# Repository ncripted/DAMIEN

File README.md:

# DAMIEN | Omni UGV

DAMIEN is a miniature omnidirectional camera rover with three independently driven omni wheels. The PCB doubles as the chassis. The design uses an ESP32-S3, a ribbon-connected camera, and a single-cell LiPo power system with USB charging and programming.

## Open the design

Open [the Rev F KiCad project](outputs/rover/Omni_UGV_Rev_F_power_rebuild/omni_ugv.kicad_pro) in KiCad. The project contains the editable schematics, board, and project-local footprint library. See the [routing checkpoint](outputs/rover/Omni_UGV_Rev_F_power_rebuild/START_HERE.md) and the [latest KiCad DRC report](outputs/rover/Omni_UGV_Rev_F_power_rebuild/drc.json).

## Prototype status

**Fabrication is on hold.** The saved Rev F rebuild has 19 open connections and 7 dangling traces. The remaining work includes charger, battery-protector, and eFuse routing, plus electrical review of the motor-current path, braking transients, and short-circuit recovery.

## Repository contents

- [Board revisions and review packages](outputs/rover/) include earlier designs and intermediate candidates.
- [Development and validation work](work/) includes layout experiments, routing scripts, and engineering checks.

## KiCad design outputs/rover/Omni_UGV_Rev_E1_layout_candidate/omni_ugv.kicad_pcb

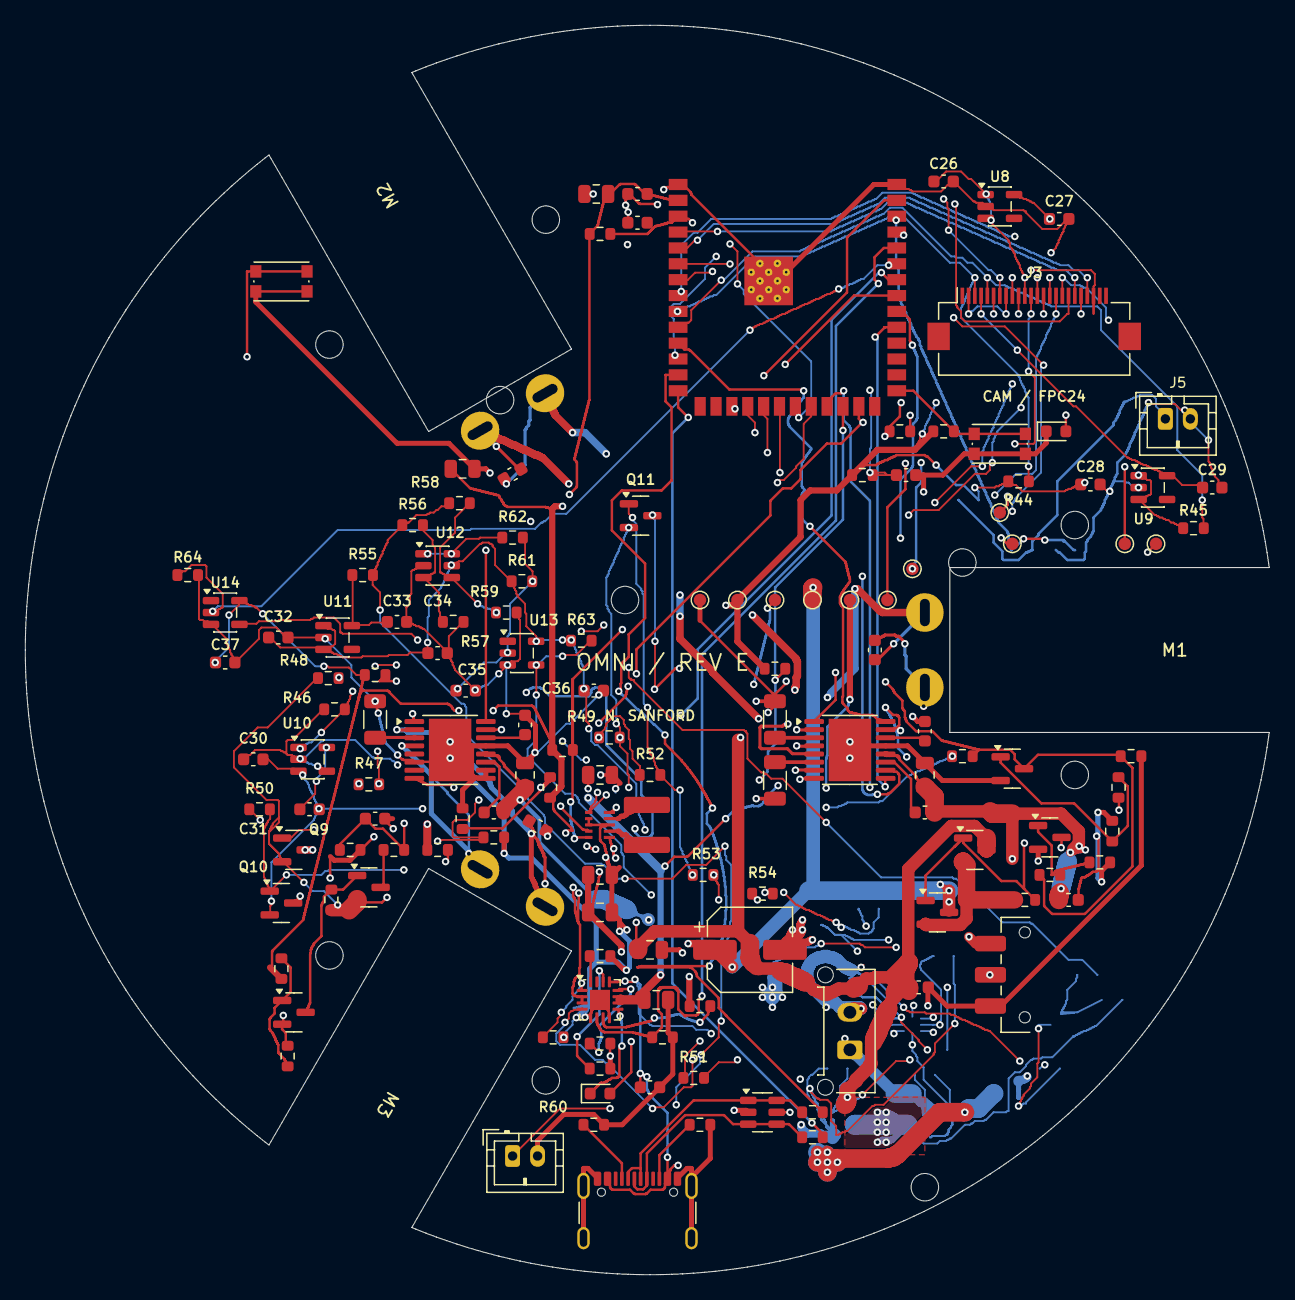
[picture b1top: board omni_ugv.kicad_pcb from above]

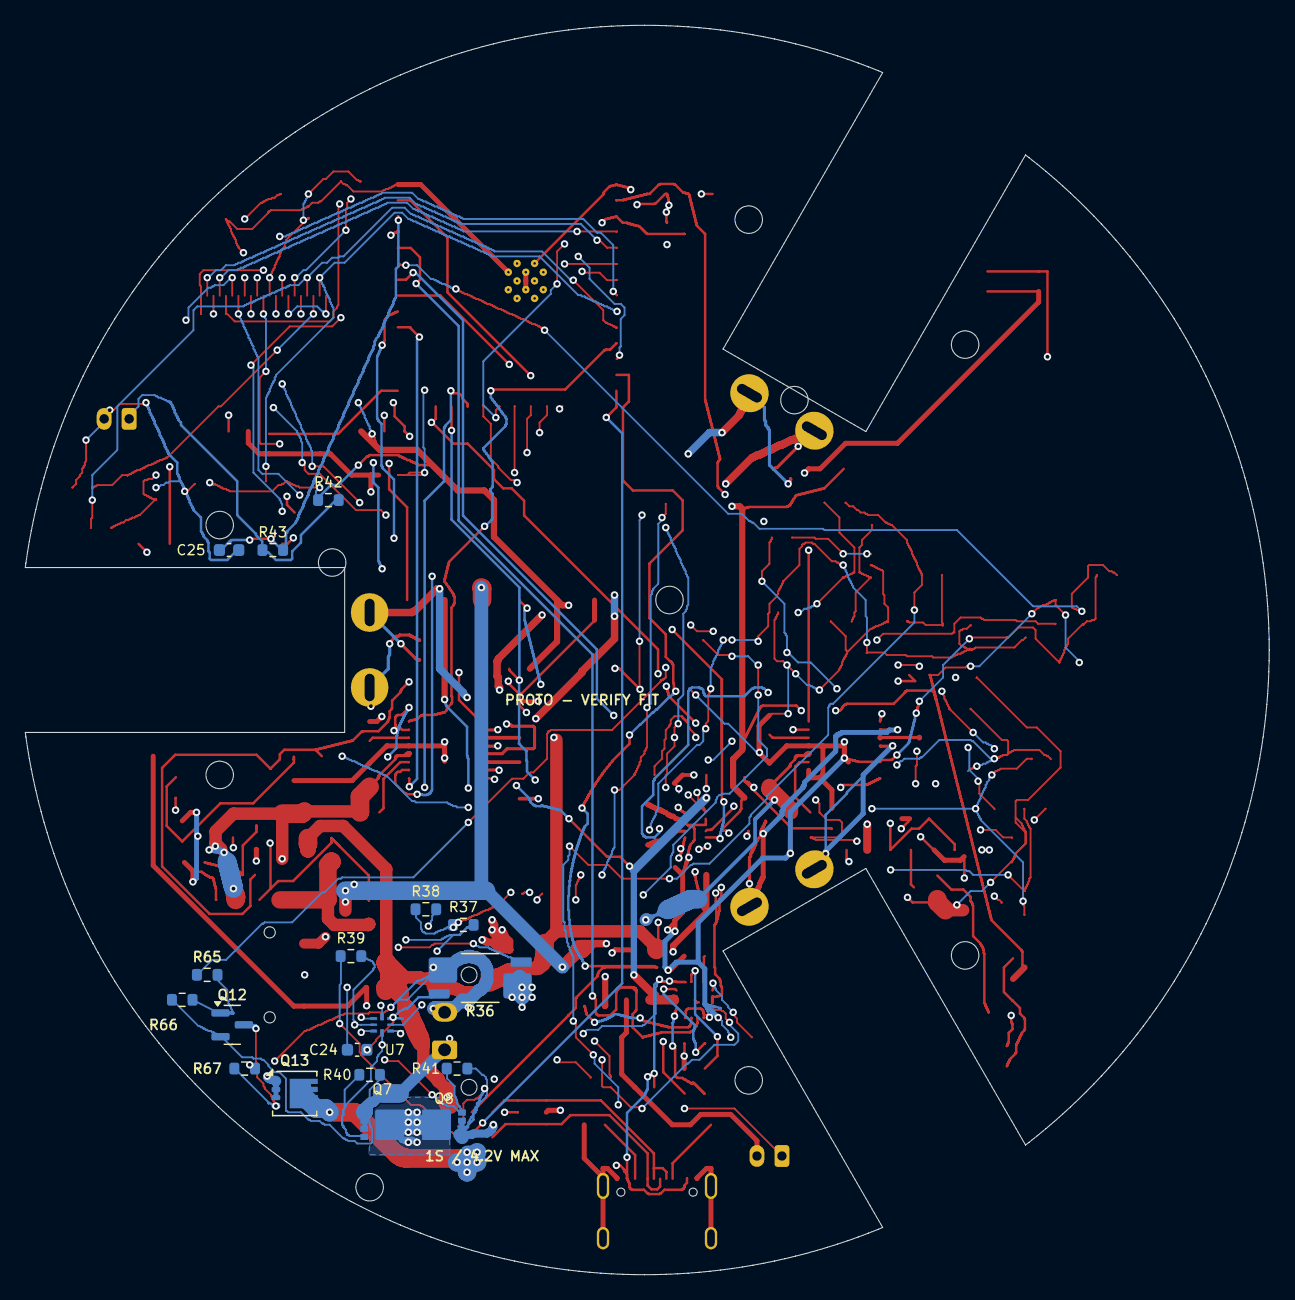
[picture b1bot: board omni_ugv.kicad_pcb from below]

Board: 4 copper layers, 99.6 x 100.0 mm, 167 parts (18 on the bottom side), 107 nets.

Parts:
C1, C15, C21: 1u/10V; Capacitor_SMD__C_0603_1608Metric
C2, C5, C6, C9, C16, C17: 10u/10V; Capacitor_SMD__C_0805_2012Metric
C3, C4, C22, C23: 100n/16V; Capacitor_SMD__C_0603_1608Metric
C7, C10: 2.2u/10V; Capacitor_SMD__C_0603_1608Metric
C8, C11: 10n/25V; Capacitor_SMD__C_0603_1608Metric
C12, C13, C14: 100n/25V; Capacitor_SMD__C_0603_1608Metric
C18, C19, C20: 22u/10V X5R 20%; Capacitor_SMD__C_0805_2012Metric
C24, C25: 100n/16V X7R; Capacitor_SMD__C_0603_1608Metric
C26, C27, C28, C29, C32, C33: 2.2u/10V X7R; Capacitor_SMD__C_0603_1608Metric
C30, C31, C34, C36, C37: 100n/10V X7R; Capacitor_SMD__C_0603_1608Metric
C35: 220n/10V X7R; Capacitor_SMD__C_0603_1608Metric
C90: 220u/10V; CP_Elec_6.3x5.8_HandAssembly
D1: STATUS GREEN; LED_SMD__LED_0603_1608Metric
D2: CHARGE AMBER; LED_SMD__LED_0603_1608Metric
H1, H2, H3, H4, H5, H6, H7, H8, H9, H10: M2; MountingHole_2.2mm_M2
J1: USB-C; Connector_USB__USB_C_Receptacle_GCT_USB4105-xx-A_16P_TopMnt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
J2: RAW 1S CELL 4.2V MAX; Connector_Molex__Molex_Micro-Fit_3.0_43650-0215_1x02_P3.00m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
J3: M0031 CAMERA FPC24; Camera_FH12_24
J4: CELL NTC - CHARGER; Connector_JST__JST_PH_B2B-PH-K_1x02_P2.00mm_Vertical
J5: CELL NTC - DRIVE; Connector_JST__JST_PH_B2B-PH-K_1x02_P2.00mm_Vertical
L1: 0.47uH/5.4A; L_XFL4015
M1: POLOLU 3065 MOTOR 1; Pololu_HPCB_Solder
M2: POLOLU 3065 MOTOR 2; Pololu_HPCB_Solder
M3: POLOLU 3065 MOTOR 3; Pololu_HPCB_Solder
Q1, Q2: DMP2035U-7; Package_TO_SOT_SMD__SOT-23
Q3, Q4, Q6, Q10, Q11: MMBT3904; Package_TO_SOT_SMD__SOT-23
Q5: AO3401A; Package_TO_SOT_SMD__SOT-23
Q7, Q8: CSD17308Q3; CSD17308Q3_TI
Q9, Q12: MMBT3906; Package_TO_SOT_SMD__SOT-23
Q13: DMP2008UFG-7; Discharge_PowerDI3333_8
R1, R2, R4, R5, R8, R29, R54: 10k; Resistor_SMD__R_0603_1608Metric
R3, R27, R62: 1k; Resistor_SMD__R_0603_1608Metric
R6, R7, R9: 0.25R/0.5W; Resistor_SMD__R_1206_3216Metric
R10, R11: 5.1k; Resistor_SMD__R_0603_1608Metric
R12, R13: 22R; Resistor_SMD__R_0603_1608Metric
R14: 3.57k; Resistor_SMD__R_0603_1608Metric
R15: 3.24k; Resistor_SMD__R_0603_1608Metric
R16: 46.4k; Resistor_SMD__R_0603_1608Metric
R17, R19, R22, R23, R26, R30, R31, R33, R34, R35, R46, R48, R61, R63, R64: 100k; Resistor_SMD__R_0603_1608Metric
R18: 2.2k; Resistor_SMD__R_0603_1608Metric
R20: 511k; Resistor_SMD__R_0603_1608Metric
R21: 91k; Resistor_SMD__R_0603_1608Metric
R24, R47: 22k; Resistor_SMD__R_0603_1608Metric
R25, R67: 56k; Resistor_SMD__R_0603_1608Metric
R28, R49, R51, R53, R66: 1M; Resistor_SMD__R_0603_1608Metric
R32, R65: 47k; Resistor_SMD__R_0603_1608Metric
R36: 10m 1% 1W KELVIN; WSK2512_T1p19_Kelvin
R37: 100R 1%; Resistor_SMD__R_0603_1608Metric
R38: 20R 1%; Resistor_SMD__R_0603_1608Metric
R39, R43: 1k 1%; Resistor_SMD__R_0603_1608Metric
R40, R41: 10M; Resistor_SMD__R_0603_1608Metric
R42, R55, R60: 10k 1%; Resistor_SMD__R_0603_1608Metric
R44, R45: 4.7k; Resistor_SMD__R_0603_1608Metric
R50: 33k; Resistor_SMD__R_0603_1608Metric
R52: 3.3k; Resistor_SMD__R_0603_1608Metric
R56: 200k 1%; Resistor_SMD__R_0603_1608Metric
R57, R59: 100k 1%; Resistor_SMD__R_0603_1608Metric
R58: 442k 1%; Resistor_SMD__R_0603_1608Metric
SW1: RESET; Button_Switch_SMD__SW_Push_1P1T_NO_CK_KMR2
SW2: BOOT; Button_Switch_SMD__SW_Push_1P1T_NO_CK_KMR2
SW3: POWER; Button_Switch_SMD__SW_SPDT_CK_JS102011SAQN
TP1: GND; TestPoint__TestPoint_Pad_D1.0mm
TP2: +3V3; TestPoint__TestPoint_Pad_D1.0mm
TP3: VBAT; TestPoint__TestPoint_Pad_D1.0mm
TP4: VMOTOR; TestPoint__TestPoint_Pad_D1.0mm
TP5: SYS_RAW; TestPoint__TestPoint_Pad_D1.0mm
TP6: ESP_EN; TestPoint__TestPoint_Pad_D1.0mm
TP7: LED_STATUS; TestPoint__TestPoint_Pad_D1.0mm
TP8: DRIVE_ENABLE; TestPoint__TestPoint_Pad_D1.0mm
TP9: FAULT_U2; TestPoint__TestPoint_Pad_D1.0mm
TP10: FAULT_U3; TestPoint__TestPoint_Pad_D1.0mm
TP11: REG_PG; TestPoint__TestPoint_Pad_D1.0mm
U1: ESP32-S3-WROOM-1-N8R8; RF_Module__ESP32-S3-WROOM-1
U2, U3: DRV8833PWP; Package_SO__HTSSOP-16-1EP_4.4x5mm_P0.65mm_EP3.4x5mm_Mask2.4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
U4: TPS63802DLA; TPS63802_DLA0010A
U5: BQ24074RGT; Package_DFN_QFN__VQFN-16-1EP_3x3mm_P0.5mm_EP1.6x1.6mm
U6: USBLC6-2SC6; Package_TO_SOT_SMD__SOT-23-6
U7: BQ298217RUGR; BQ298217_RUG0008A
U8: TLV75513PDBVR; Camera_SOT23_5
U9: TLV75528PDBVR; Camera_SOT23_5
U10: TPS3840DL31DBVR; Camera_SOT23_5
U11: TLV75533PDBVR; Camera_SOT23_5
U12: TLV6700DDCR; Power_SOT23_6
U13: SN74LVC1G14DBVR; Camera_SOT23_5
U14: SN74LVC1G17DBVR; Camera_SOT23_5

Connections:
+3V3: C2.1, C3.1, C5.1, C19.1, C20.1, C26.1, C28.1, C37.1, J3.11, R1.1, R2.1, R4.1, R5.1, R8.1, R19.1, R20.1, R22.1, R32.1, R42.1, R44.1, R45.1, TP2.1, U1.2, U4.6, U8.1, U8.3, U9.1, U9.3, U14.5
CAM_1V3: C27.1, J3.10, U8.5
CAM_2V8: C29.1, J3.4, U9.5
CAM_D0: J3.19, U1.4
CAM_D1: J3.21, U1.5
CAM_D2: J3.22, U1.6
CAM_D3: J3.20, U1.7
CAM_D4: J3.18, U1.12
CAM_D5: J3.16, U1.17
CAM_D6: J3.14, U1.18
CAM_D7: J3.12, U1.19
CAM_HREF: J3.9, U1.22
CAM_PCLK: J3.17, U1.20
CAM_RESET: C4.1, J3.6, R4.2
CAM_SCL: J3.5, R45.2, U1.10
CAM_SDA: J3.3, R44.2, U1.9
CAM_VSYNC: J3.7, U1.21
CAM_XCLK: J3.13, U1.8
CELL_CHG_TEMP: J4.1, R55.2, R56.1, R58.1
CELL_N: C30.2, C31.2, J2.2, Q10.2, Q11.2, R36.1, R49.2, R51.2, R53.2, R67.2, U7.5, U10.3
CELL_P: C30.1, J2.1, Q7.1, Q7.2, Q7.3, Q12.2, R37.1, R38.1, R40.2, R46.1, R66.1, U10.2, U10.4
CELL_TEMP_ADC: C25.1, R43.2, U1.38
CELL_TEMP_DIV: J5.1, R42.2, R43.1
CELL_UV_CT: C31.1, U10.5
CELL_UV_EN_B: Q10.1, R50.2, R51.1
CELL_UV_FAULT: Q9.3, R49.1, R50.1, R52.1
CELL_UV_MOTOR_B: Q11.1, R52.2, R53.1
CELL_UV_PNP_B: Q9.1, R47.2, R48.2
CELL_UV_RESET_N: R46.2, R47.1, R65.1, U10.1
CHG_3V3: C33.1, R55.1, U11.5
CHG_COLD_SENSE: R58.2, R59.1, U12.4
CHG_DISABLE: R63.2, U5.4, U13.4
CHG_HOT_SENSE: R56.2, R57.1, U12.3
CHG_ILIM: R15.1, U5.12
CHG_ISET: R14.1, U5.16
CHG_LED_A: D2.2, R18.2
CHG_PGOOD: R19.2, U5.7
CHG_STATUS: D2.1, U5.9
CHG_TEMP_ALLOW_RC: C35.1, R61.2, R62.2, U13.2
CHG_TEMP_OK_OD: R62.1, U12.1, U12.6
CHG_TIMER: R16.1, U5.14
CHG_TS_BIAS: R60.1, U5.1
CUT_GATE: Q12.3, Q13.4, R67.1
CUT_PNP_B: Q12.1, R65.2, R66.2
DRIVE_ENABLE: Q4.3, Q11.3, R25.1, R27.2, R28.1, TP8.1, U2.1, U3.1
DRIVE_REQ: R27.1, U14.4
DRIVE_REQ_RAW: R64.1, U1.35, U14.2
ESP_BOOT: R2.2, SW2.1, U1.27
ESP_EN: C1.1, R1.2, SW1.1, TP6.1, U1.3
FAULT_U2: R5.2, TP9.1, U1.24, U2.8
FAULT_U3: R8.2, TP10.1, U1.25, U3.8
GND: C1.2, C2.2, C3.2, C4.2, C5.2, C6.2, C7.2, C9.2, C10.2, C15.2, C16.2, C17.2, C18.2, C19.2, C20.2, C21.2, C22.2, C23.2, C25.2, C26.2, C27.2, C28.2, C29.2, C32.2, C33.2, C34.2, C35.2, C36.2, C37.2, C90.2, D1.1, J1.A1, J1.A12, J1.B1, J1.B12, J1.S1, J3.2, J3.8, J3.15, J4.2, J5.2, Q3.2, Q4.2, Q6.2, R6.2, R7.2, R9.2, R10.2, R11.2, R14.2, R15.2, R16.2, R17.2, R21.2, R23.2, R26.2, R28.2, R30.2, R33.2, R35.2, R36.2, R57.2, R59.2, R60.2, R64.2, SW1.2, SW2.2, SW3.1, TP1.1, U1.1, U1.40, U1.41, U2.13, U2.17, U3.6, U3.9, U3.10, U3.13, U3.17, U4.2, U4.3, U4.8, U5.5, U5.8, U5.17, U6.2, U8.2, U9.2, U11.2, U12.2, U13.3, U14.3
LED_A: D1.2, R3.2
LED_STATUS: R3.1, TP7.1, U1.37
M1_A: C12.1, M1.1, U2.2
M1_B: C12.2, M1.2, U2.4
M1_IN1: U1.11, U2.16
M1_IN2: U1.23, U2.15
M1_SENSE: R6.1, U2.3
M2_A: C13.1, M2.1, U2.7
M2_B: C13.2, M2.2, U2.5
M2_IN1: U1.31, U2.9
M2_IN2: U1.32, U2.10
M2_SENSE: R7.1, U2.6
M3_A: C14.1, M3.1, U3.2
M3_B: C14.2, M3.2, U3.4
M3_IN1: U1.33, U3.16
M3_IN2: U1.34, U3.15
M3_SENSE: R9.1, U3.3
MEAS_BASE: Q6.1, R32.2, R33.1
MEAS_GATE: Q5.1, Q6.3, R31.2
MOTOR_BASE: Q3.1, R25.2, R26.1
MOTOR_GATE: Q1.1, Q2.1, Q3.3, R24.2
MOTOR_MID: Q1.2, Q2.2, R24.1
PROTECTED_RAW: Q8.1, Q8.2, Q8.3, Q13.1, Q13.2, Q13.3, R39.1, R41.2
PROT_BAT: R38.2, U7.1
PROT_CHG: Q7.4, R40.1, U7.8
PROT_CS_SENSE: R36.4, U7.4
PROT_DRAIN: Q7.5, Q7.6, Q7.7, Q7.8, Q7.9, Q8.5, Q8.6, Q8.7, Q8.8, Q8.9
PROT_DSG: Q8.4, R41.1, U7.7
PROT_PACK: R39.2, U7.6
PROT_VDD: C24.1, R37.2, U7.2
PROT_VSS_SENSE: C24.2, R36.3, U7.3
REG_FB: R20.2, R21.1, U4.4
REG_L1: L1.1, U4.9
REG_L2: L1.2, U4.7
REG_PG: R22.2, TP11.1, U4.5
SYS_ON: Q10.3, R23.1, R54.2, U4.1
SYS_ON_REQ: R54.1, SW3.2
SYS_RAW: C17.1, C18.1, R18.1, SW3.3, TP5.1, U4.10, U5.10, U5.11
U2_VCP: C8.1, U2.11
U2_VINT: C7.1, U2.14
U3_VCP: C11.1, U3.11
U3_VINT: C10.1, U3.14
USB_5V: C15.1, C32.1, C34.1, C36.1, J1.A4, J1.A9, J1.B4, J1.B9, R29.1, R61.1, R63.1, U5.13, U6.5, U11.1, U11.3, U12.5, U13.5
USB_500_ENABLE: R17.1, U1.36, U5.6
USB_CC1: J1.A5, R10.1
USB_CC2: J1.B5, R11.1
USB_DETECT_BASE: Q4.1, R29.2, R30.1
USB_DM: R12.2, U1.13
USB_DM_EXT: J1.A7, J1.B7, R12.1, U6.1, U6.6
USB_DP: R13.2, U1.14
USB_DP_EXT: J1.A6, J1.B6, R13.1, U6.3, U6.4
VBAT: C16.1, C21.1, Q1.3, Q5.2, Q9.2, Q13.5, R31.1, R48.1, TP3.1, U5.2, U5.3
VBAT_ADC: C23.1, R34.2, R35.1, U1.39
VBAT_MEAS: Q5.3, R34.1
VMOTOR: C6.1, C8.2, C9.1, C11.2, C22.1, C90.1, Q2.3, TP4.1, U2.12, U3.12

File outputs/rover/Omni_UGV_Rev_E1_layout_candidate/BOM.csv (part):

Reference,Value,MPN,Footprint,Notes
U1,ESP32-S3-WROOM-1-N8R8,ESP32-S3-WROOM-1-N8R8,UGV:RF_Module__ESP32-S3-WROOM-1,
R1,10k,,UGV:Resistor_SMD__R_0603_1608Metric,
C1,1u/10V,,UGV:Capacitor_SMD__C_0603_1608Metric,
R2,10k,,UGV:Resistor_SMD__R_0603_1608Metric,
C2,10u/10V,,UGV:Capacitor_SMD__C_0805_2012Metric,
C3,100n/16V,,UGV:Capacitor_SMD__C_0603_1608Metric,
SW1,RESET,KMR221GLFS,UGV:Button_Switch_SMD__SW_Push_1P1T_NO_CK_KMR2,
SW2,BOOT,KMR221GLFS,UGV:Button_Switch_SMD__SW_Push_1P1T_NO_CK_KMR2,
R3,1k,,UGV:Resistor_SMD__R_0603_1608Metric,
D1,STATUS GREEN,0603 green LED,UGV:LED_SMD__LED_0603_1608Metric,
R4,10k,,UGV:Resistor_SMD__R_0603_1608Metric,
C4,100n/16V,,UGV:Capacitor_SMD__C_0603_1608Metric,
C5,10u/10V,,UGV:Capacitor_SMD__C_0805_2012Metric,
U2,DRV8833PWP,DRV8833PWPR,UGV:Package_SO__HTSSOP-16-1EP_4.4x5mm_P0.65mm_EP3.4x5mm_Mask2.46x2.31mm,
C6,10u/10V,,UGV:Capacitor_SMD__C_0805_2012Metric,
C7,2.2u/10V,,UGV:Capacitor_SMD__C_0603_1608Metric,
C8,10n/25V,,UGV:Capacitor_SMD__C_0603_1608Metric,
R5,10k,,UGV:Resistor_SMD__R_0603_1608Metric,
R6,0.25R/0.5W,,UGV:Resistor_SMD__R_1206_3216Metric,
R7,0.25R/0.5W,,UGV:Resistor_SMD__R_1206_3216Metric,
U3,DRV8833PWP,DRV8833PWPR,UGV:Package_SO__HTSSOP-16-1EP_4.4x5mm_P0.65mm_EP3.4x5mm_Mask2.46x2.31mm,
C9,10u/10V,,UGV:Capacitor_SMD__C_0805_2012Metric,
C10,2.2u/10V,,UGV:Capacitor_SMD__C_0603_1608Metric,
C11,10n/25V,,UGV:Capacitor_SMD__C_0603_1608Metric,
R8,10k,,UGV:Resistor_SMD__R_0603_1608Metric,
R9,0.25R/0.5W,,UGV:Resistor_SMD__R_1206_3216Metric,
M1,POLOLU 3065 MOTOR 1,Pololu 3065,UGV:Pololu_HPCB_Solder,Terminal slots require physical fit check; use separate printed clamps
C12,100n/25V,,UGV:Capacitor_SMD__C_0603_1608Metric,
M2,POLOLU 3065 MOTOR 2,Pololu 3065,UGV:Pololu_HPCB_Solder,Terminal slots require physical fit check; use separate printed clamps
C13,100n/25V,,UGV:Capacitor_SMD__C_0603_1608Metric,
M3,POLOLU 3065 MOTOR 3,Pololu 3065,UGV:Pololu_HPCB_Solder,Terminal slots require physical fit check; use separate printed clamps
C14,100n/25V,,UGV:Capacitor_SMD__C_0603_1608Metric,
C90,220u/10V,Panasonic EEEFT1A221AP,UGV:CP_Elec_6.3x5.8_HandAssembly,"6.3mm diameter, 5.8mm high; oversized hand-assembly lands; approved 220-470uF bulk range; check actual PWM ripple"
J1,USB-C,GCT USB4105-GF-A,UGV:Connector_USB__USB_C_Receptacle_GCT_USB4105-xx-A_16P_TopMnt_Horizontal,
R10,5.1k,,UGV:Resistor_SMD__R_0603_1608Metric,
R11,5.1k,,UGV:Resistor_SMD__R_0603_1608Metric,
U6,USBLC6-2SC6,USBLC6-2SC6,UGV:Package_TO_SOT_SMD__SOT-23-6,
R12,22R,,UGV:Resistor_SMD__R_0603_1608Metric,
R13,22R,,UGV:Resistor_SMD__R_0603_1608Metric,
U5,BQ24074RGT,BQ24074RGTR,UGV:Package_DFN_QFN__VQFN-16-1EP_3x3mm_P0.5mm_EP1.6x1.6mm,
R14,3.57k,,UGV:Resistor_SMD__R_0603_1608Metric,
R15,3.24k,,UGV:Resistor_SMD__R_0603_1608Metric,
R16,46.4k,,UGV:Resistor_SMD__R_0603_1608Metric,
R17,100k,,UGV:Resistor_SMD__R_0603_1608Metric,
C15,1u/10V,,UGV:Capacitor_SMD__C_0603_1608Metric,
C16,10u/10V,,UGV:Capacitor_SMD__C_0805_2012Metric,
C17,10u/10V,,UGV:Capacitor_SMD__C_0805_2012Metric,
J2,RAW 1S CELL 4.2V MAX,Molex 43650-0215,UGV:Connector_Molex__Molex_Micro-Fit_3.0_43650-0215_1x02_P3.00mm_Vertical,"Raw cell input, pin1 positive; protection now onboard. Cell itself must support >=4A continuous / >=5A peak. No CELL_N-to-GND bypass."
J4,CELL NTC - CHARGER,JST B2B-PH-K-S,UGV:Connector_JST__JST_PH_B2B-PH-K_1x02_P2.00mm_Vertical,"Independent insulated 103AT-2 bonded to actual cell. Analog U12 window controls U5 CE; pin1 CELL_CHG_TEMP, pin2 GND. Never attach to raw CELL_N."
D2,CHARGE AMBER,,UGV:LED_SMD__LED_0603_1608Metric,
R18,2.2k,,UGV:Resistor_SMD__R_0603_1608Metric,
R19,100k,,UGV:Resistor_SMD__R_0603_1608Metric,
U4,TPS63802DLA,TPS63802DLAR,UGV:TPS63802_DLA0010A,
L1,0.47uH/5.4A,Coilcraft XFL4015-471MEC,UGV:L_XFL4015,
C18,22u/10V X5R 20%,C2012X5R1A226M125AB,UGV:Capacitor_SMD__C_0805_2012Metric,"TDK production 0805, 22uF 10V +/-20% X5R. DC-bias/temperature/aging verification required; nominal capacitance is not effective capacitance."
C19,22u/10V X5R 20%,C2012X5R1A226M125AB,UGV:Capacitor_SMD__C_0805_2012Metric,"TDK production 0805, 22uF 10V +/-20% X5R. DC-bias/temperature/aging verification required; nominal capacitance is not effective capacitance."
C20,22u/10V X5R 20%,C2012X5R1A226M125AB,UGV:Capacitor_SMD__C_0805_2012Metric,"TDK production 0805, 22uF 10V +/-20% X5R. DC-bias/temperature/aging verification required; nominal capacitance is not effective capacitance."
R20,511k,,UGV:Resistor_SMD__R_0603_1608Metric,
R21,91k,,UGV:Resistor_SMD__R_0603_1608Metric,
R22,100k,,UGV:Resistor_SMD__R_0603_1608Metric,
R23,100k,,UGV:Resistor_SMD__R_0603_1608Metric,
SW3,POWER,C&K JS102011SAQN,UGV:Button_Switch_SMD__SW_SPDT_CK_JS102011SAQN,
Q1,DMP2035U-7,DMP2035U-7,UGV:Package_TO_SOT_SMD__SOT-23,"Lower-loss P-FET, same G1/S2/D3 SOT23. Thermal/braking qualification remains required."
Q2,DMP2035U-7,DMP2035U-7,UGV:Package_TO_SOT_SMD__SOT-23,"Lower-loss P-FET, same G1/S2/D3 SOT23. Thermal/braking qualification remains required."
Q5,AO3401A,AO3401A,UGV:Package_TO_SOT_SMD__SOT-23,
Q3,MMBT3904,MMBT3904,UGV:Package_TO_SOT_SMD__SOT-23,
Q4,MMBT3904,MMBT3904,UGV:Package_TO_SOT_SMD__SOT-23,
Q6,MMBT3904,MMBT3904,UGV:Package_TO_SOT_SMD__SOT-23,
R24,22k,,UGV:Resistor_SMD__R_0603_1608Metric,
R25,56k,,UGV:Resistor_SMD__R_0603_1608Metric,
R26,100k,,UGV:Resistor_SMD__R_0603_1608Metric,
R27,1k,,UGV:Resistor_SMD__R_0603_1608Metric,
R28,1M,,UGV:Resistor_SMD__R_0603_1608Metric,
R29,10k,,UGV:Resistor_SMD__R_0603_1608Metric,
R30,100k,,UGV:Resistor_SMD__R_0603_1608Metric,
C21,1u/10V,,UGV:Capacitor_SMD__C_0603_1608Metric,
C22,100n/16V,,UGV:Capacitor_SMD__C_0603_1608Metric,
R31,100k,,UGV:Resistor_SMD__R_0603_1608Metric,
R32,47k,,UGV:Resistor_SMD__R_0603_1608Metric,
R33,100k,,UGV:Resistor_SMD__R_0603_1608Metric,
R34,100k,,UGV:Resistor_SMD__R_0603_1608Metric,
R35,100k,,UGV:Resistor_SMD__R_0603_1608Metric,
C23,100n/16V,,UGV:Capacitor_SMD__C_0603_1608Metric,
TP1,GND,,UGV:TestPoint__TestPoint_Pad_D1.0mm,
TP2,+3V3,,UGV:TestPoint__TestPoint_Pad_D1.0mm,
TP3,VBAT,,UGV:TestPoint__TestPoint_Pad_D1.0mm,
TP4,VMOTOR,,UGV:TestPoint__TestPoint_Pad_D1.0mm,
TP5,SYS_RAW,,UGV:TestPoint__TestPoint_Pad_D1.0mm,
TP6,ESP_EN,,UGV:TestPoint__TestPoint_Pad_D1.0mm,
TP7,LED_STATUS,,UGV:TestPoint__TestPoint_Pad_D1.0mm,GPIO43 status LED test point; UART0 TX no longer exposed. Programming remains native USB.
TP8,DRIVE_ENABLE,,UGV:TestPoint__TestPoint_Pad_D1.0mm,
TP9,FAULT_U2,,UGV:TestPoint__TestPoint_Pad_D1.0mm,
TP10,FAULT_U3,,UGV:TestPoint__TestPoint_Pad_D1.0mm,
TP11,REG_PG,,UGV:TestPoint__TestPoint_Pad_D1.0mm,
U7,BQ298217RUGR,BQ298217RUGR,UGV:BQ298217_RUG0008A,Primary BQ298217: factory UV 2.6V; cold-start/wake compatibility open. CS/VSS use R36 voltage contacts. PACK senses PROTECTED_RAW before Q13.
Q7,CSD17308Q3,CSD17308Q3,UGV:CSD17308Q3_TI,"Primary charge FET: source CELL_P, common drain PROT_DRAIN."
Q8,CSD17308Q3,CSD17308Q3,UGV:CSD17308Q3_TI,Primary discharge FET. E1 uses separate off-pad power and sense vias.
R36,10m 1% 1W KELVIN,WSK2512R0100FEA,UGV:WSK2512_T1p19_Kelvin,"4-terminal Vishay WSK2512 10mΩ. Current pads1/2, independent sense3/4. Native numbering explicitly mapped to manufacturer land drawing."
R37,100R 1%,,UGV:Resistor_SMD__R_0603_1608Metric,
R38,20R 1%,,UGV:Resistor_SMD__R_0603_1608Metric,
R39,1k 1%,,UGV:Resistor_SMD__R_0603_1608Metric,"U7 PACK sense from PROTECTED_RAW, upstream of secondary Q13."
C24,100n/16V X7R,,UGV:Capacitor_SMD__C_0603_1608Metric,"U7 VDD decoupling returns to PROT_VSS_SENSE, not the main GND plane."
R40,10M,,UGV:Resistor_SMD__R_0603_1608Metric,Q7 gate-source bias to raw CELL_P.
R41,10M,,UGV:Resistor_SMD__R_0603_1608Metric,Q8 gate-source bias to PROTECTED_RAW.
J5,CELL NTC - DRIVE,B2B-PH-K-S,UGV:Connector_JST__JST_PH_B2B-PH-K_1x02_P2.00mm_Vertical,Second electrically isolated103AT-2 probe bonded to same cell; not shared with J4
R42,10k 1%,,UGV:Resistor_SMD__R_0603_1608Metric,
R43,1k 1%,,UGV:Resistor_SMD__R_0603_1608Metric,
C25,100n/16V X7R,,UGV:Capacitor_SMD__C_0603_1608Metric,
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
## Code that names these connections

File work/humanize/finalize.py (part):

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
## Cell and temperature interface

J2 pin1 CELL_P, pin2 CELL_N feed onboard protection. Protected VBAT supplies the charger BAT connection and motor-power switching. Motor current does not pass through charger OUT/SYS_RAW. R36 is the intended raw-negative to system-ground connection.

J4 and J5 each use an independent electrically insulated two-wire 103AT-2 probe bonded to the cell. J4 serves charger TS. J5 feeds GPIO1/ADC1 through R42/R43/C25. GPIO43 now drives the status LED; native USB programming remains available.

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
Charging and motor paths differ: protected VBAT feeds the motor switch directly and also the charger BAT pins. Charger OUT/SYS_RAW feeds logic regulation. Motor-current qualification cannot be inferred from the charger's approximately 249 mA charging setting.

Rule checks currently pass with zero violations; no thermal, transient, physical-fit, carpet or firmware claim follows from that result. Native schematic and PCB are authoritative over older notes.
''')
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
